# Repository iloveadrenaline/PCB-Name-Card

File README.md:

# PCB-Name-Card

A name card made for hackathons with a pcb and some components that is funded by #Solder ( More on that at the end)
This is my 3rd time using KiCad  , before this I made a macropad and a clock ( Check my repos for those)
If you are just starting out this is a begginer friendly cool project , just give it a try .

---

## Overview

**PCB Name Card** is a namecard  made from a pcb that shows a short overview about me and that has blinking LEDS because why not? 
**Timelapse link** : https://lapse.hackclub.com/timelapse/6II9IPPDLHkS
## Features

-Blinking Leds

-Each component is labeled

-QR code for contact information

-Keychain Hole at the right top corner

## PCB Schematics & PCB

## Bill of Materials (BOM)

1x 555 Timer
3x ThT LEDS
3x 470 Ω Resistors
2x 4.7kΩ Resistors

## Repository Structure

```
PCB-Name-Card/
├── README.md
├── LICENSE
├── pcb/
    ├── soldernameplate.kicad_pro
    ├── soldernameplate.kicad_sch
    ├── soldernameplate.kicad_pcb
    └── gerbers/

```

## Assembly

1. Order PCB  via JLCPCB or PCBWay using the Gerber
2. Solder The components 
3. Put battery in
4. Enjoy!

## License

This project is released under the MIT License -- see in the repo

## Credits

- Built for [Hack Club's Solder](https://solder.hackclub.com/) YSWS program
- Designed by [iloveadrenaline](https://github.com/iloveadrenaline)
- Slack username : iloveadrenaline
-Claude was used for debbuging and some informations

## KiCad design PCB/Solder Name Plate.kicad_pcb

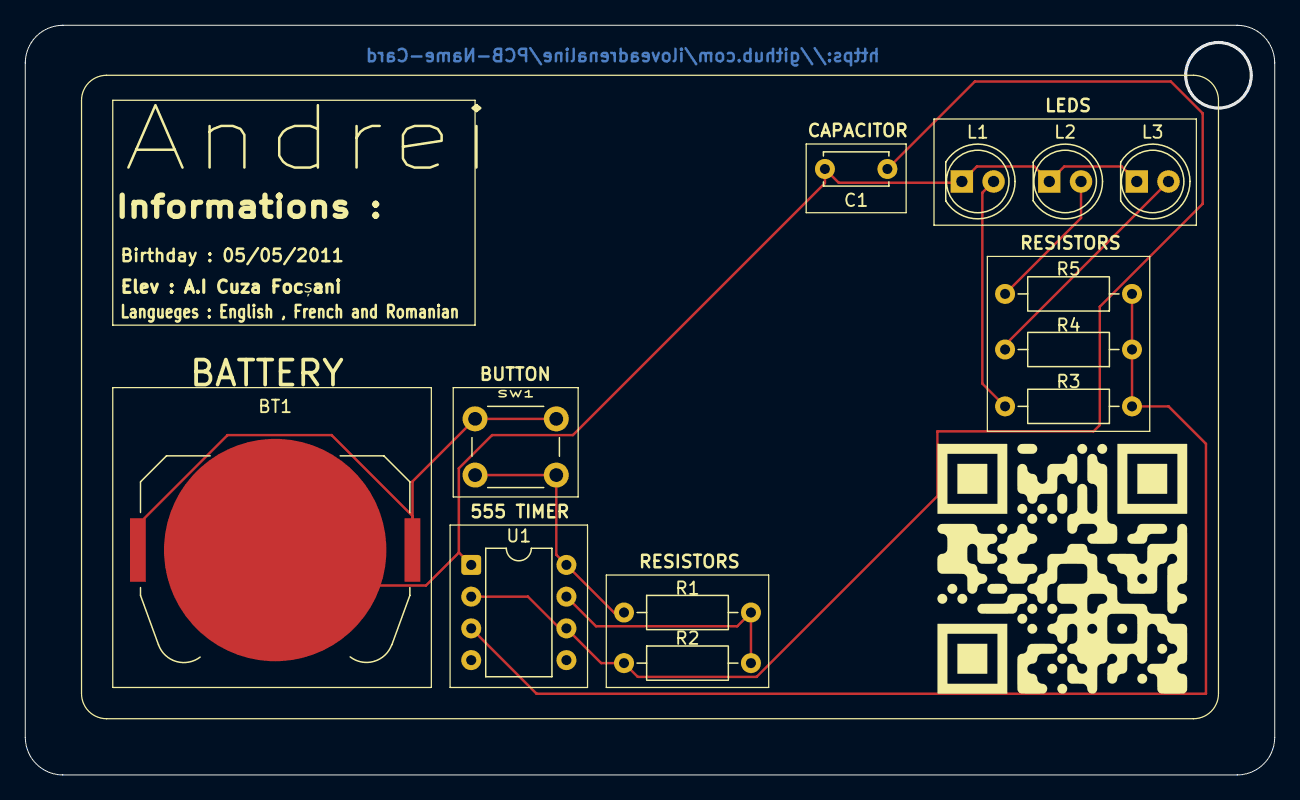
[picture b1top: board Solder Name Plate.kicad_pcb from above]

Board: 2 copper layers, 100.0 x 60.0 mm, 12 parts (0 on the bottom side), 9 nets.

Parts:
BT1: Battery_Cell; BatteryHolder_Keystone_3034_1x20mm
C1: 10μF; C_Disc_D5.0mm_W2.5mm_P5.00mm
L1, L2, L3: LED; LED_D5.0mm
R1, R2: 4.7kΩ; R_Axial_DIN0207_L6.3mm_D2.5mm_P10.16mm_Horizontal
R3, R4, R5: 470Ω; R_Axial_DIN0207_L6.3mm_D2.5mm_P10.16mm_Horizontal
SW1: Button; SW_PUSH_6mm
U1: ICM7555xP; DIP-8_W7.62mm

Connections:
unnamed: BT1.1 (+), SW1.1
unnamed: BT1.2 (-), C1.2, L1.1 (K), L2.1 (K), L3.1 (K), U1.1 (GND)
unnamed: L1.2 (A), R3.2
unnamed: L2.2 (A), R5.2
unnamed: L3.2 (A), R4.2
unnamed: R1.2, R2.2, U1.7 (DISCH)
unnamed: R3.1, R4.1, R5.1, U1.3 (OUT)
unnamed: C1.1, R2.1, U1.2 (TRIG), U1.6 (THRES)
unnamed: R1.1, SW1.2, U1.8 (VCC)
